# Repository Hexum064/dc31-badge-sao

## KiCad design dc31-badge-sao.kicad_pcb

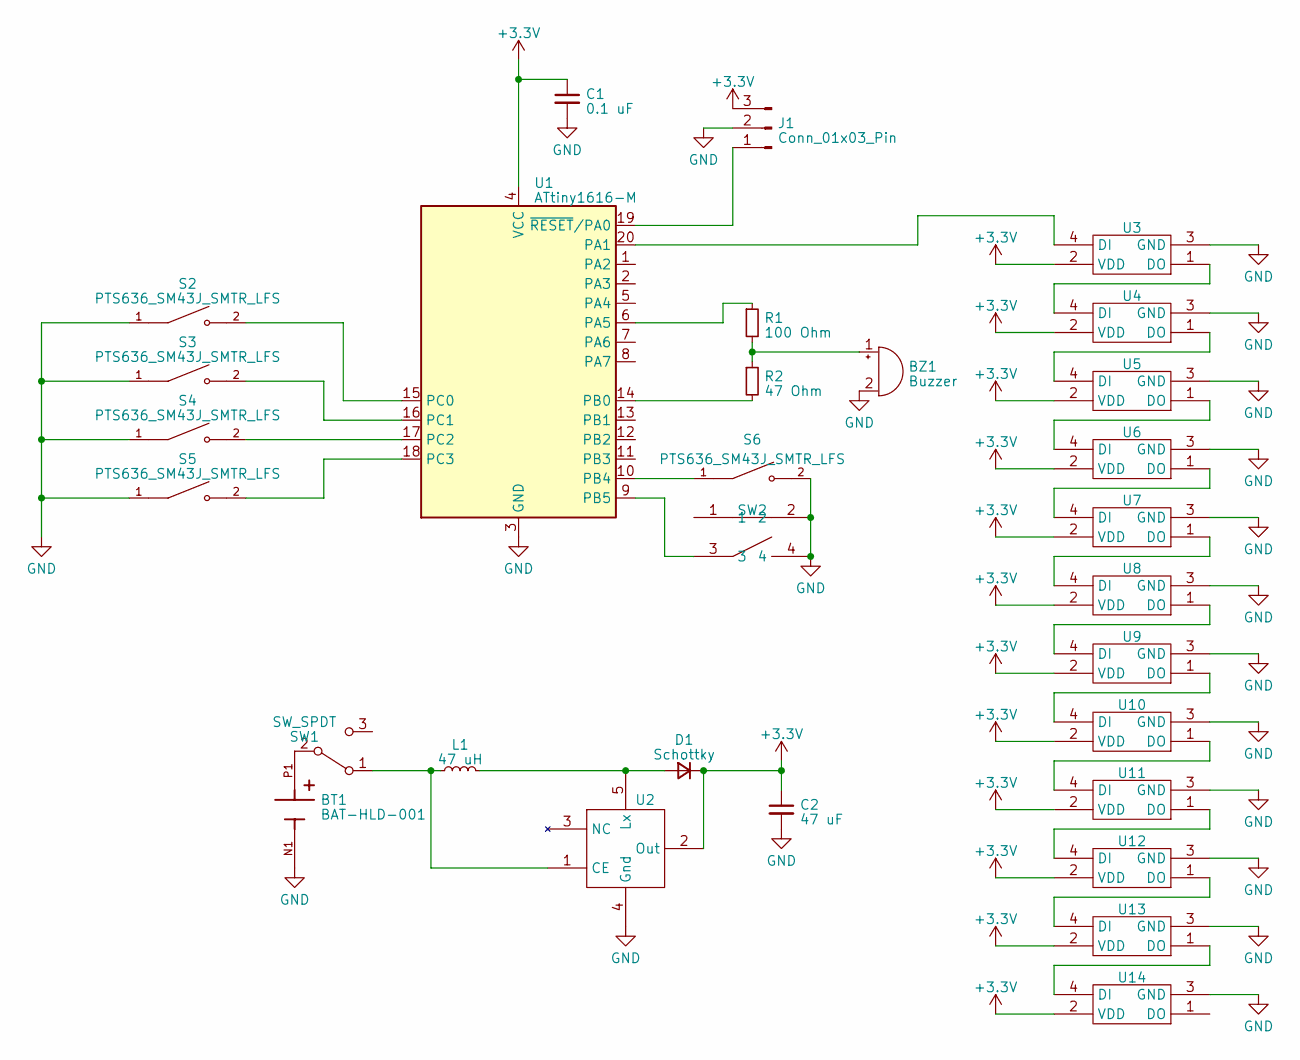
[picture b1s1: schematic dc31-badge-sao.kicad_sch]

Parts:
BT1: BAT-HLD-001; BAT_BAT-HLD-001; PARTREV C
BZ1: Buzzer; GSC1031YB-3V4000
C1: 0.1 uF; C_0603_1608Metric
C2: 47 uF; CP_EIA-3528-21_Kemet-B
D1: Schottky; D_SOD-323
J1: Conn_01x03_Pin; PinHeader_1x03_P2.54mm_Vertical
L1: 47 uH; L_0805_2012Metric
R1: 100 Ohm; R_0603_1608Metric
R2: 47 Ohm; R_0603_1608Metric
S2, S3, S4, S5, S6: PTS636_SM43J_SMTR_LFS; SW_PTS636_SM43J_SMTR_LFS; PARTREV 27 mar 19
SW1: SW_SPDT; MSS3VTR
SW2: TM-1627A
U1: ATtiny1616-M; VQFN-20-1EP_3x3mm_P0.4mm_EP1.7x1.7mm
U2: SOT-23-5
U3, U4, U5, U6, U7, U8, U9, U10, U11, U12, U13, U14: ws2812b-1010

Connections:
+3.3V: C1.1, C2.1, D1.1 (K), J1.3, L1.1, SW1.1 (A), U1.4 (VCC), U2.1 (CE), U2.2 (Out), U3.2 (VDD), U4.2 (VDD), U5.2 (VDD), U6.2 (VDD), U7.2 (VDD), U8.2 (VDD), U9.2 (VDD), U10.2 (VDD), U11.2 (VDD), U12.2 (VDD), U13.2 (VDD), U14.2 (VDD)
GND: BT1.N1, BZ1.2 (+), C1.2, C2.2, J1.2, S2.1, S3.1, S4.1, S5.1, S6.2, SW2.2, SW2.4, U1.3 (GND), U1.21 (GND), U2.4 (Gnd), U3.3 (GND), U4.3 (GND), U5.3 (GND), U6.3 (GND), U7.3 (GND), U8.3 (GND), U9.3 (GND), U10.3 (GND), U11.3 (GND), U12.3 (GND), U13.3 (GND), U14.3 (GND)
unnamed: BZ1.1 (-), R1.2, R2.1
unnamed: D1.2 (A), L1.2, U2.5 (Lx)
unnamed: J1.1, U1.19 (~RESET/PA0)
unnamed: BT1.P1, SW1.2 (B)
unnamed: U1.20 (PA1), U3.4 (DI)
unnamed: R1.1, U1.6 (PA5)
unnamed: R2.2, U1.14 (PB0)
unnamed: S6.1, U1.10 (PB4)
unnamed: SW2.3, U1.9 (PB5)
unnamed: S2.2, U1.15 (PC0)
unnamed: S3.2, U1.16 (PC1)
unnamed: S4.2, U1.17 (PC2)
unnamed: S5.2, U1.18 (PC3)
unnamed: U3.1 (DO), U4.4 (DI)
unnamed: U4.1 (DO), U5.4 (DI)
unnamed: U5.1 (DO), U6.4 (DI)
unnamed: U6.1 (DO), U7.4 (DI)
unnamed: U7.1 (DO), U8.4 (DI)
unnamed: U8.1 (DO), U9.4 (DI)
unnamed: U9.1 (DO), U10.4 (DI)
unnamed: U10.1 (DO), U11.4 (DI)
unnamed: U11.1 (DO), U12.4 (DI)
unnamed: U12.1 (DO), U13.4 (DI)
unnamed: U13.1 (DO), U14.4 (DI)

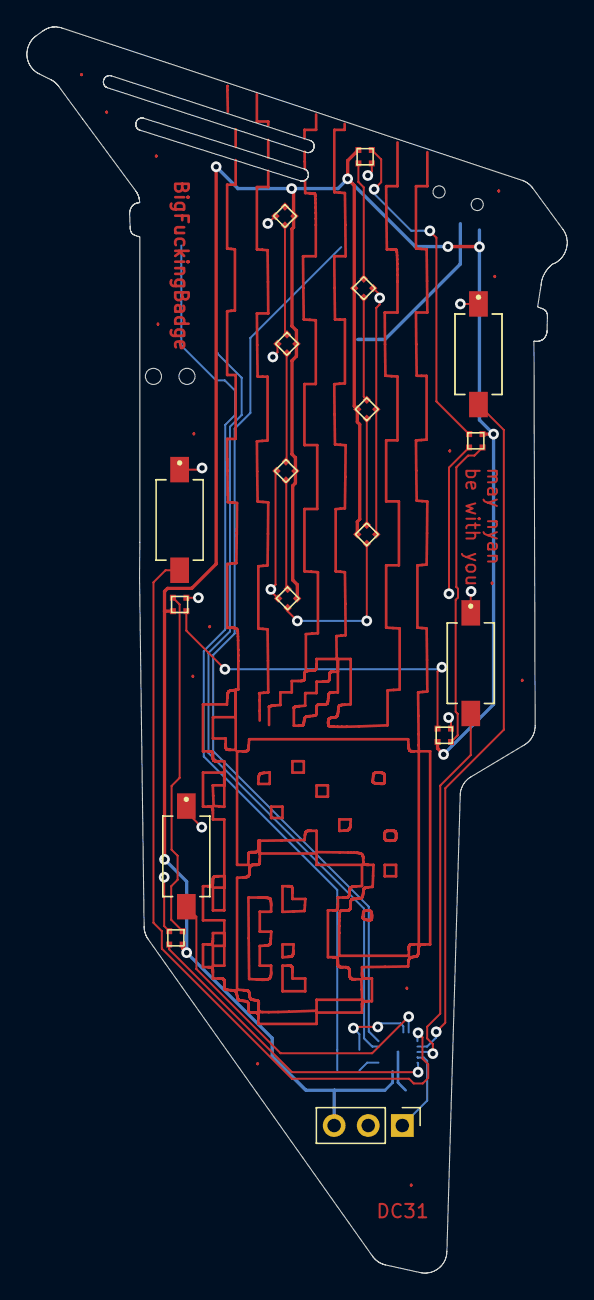
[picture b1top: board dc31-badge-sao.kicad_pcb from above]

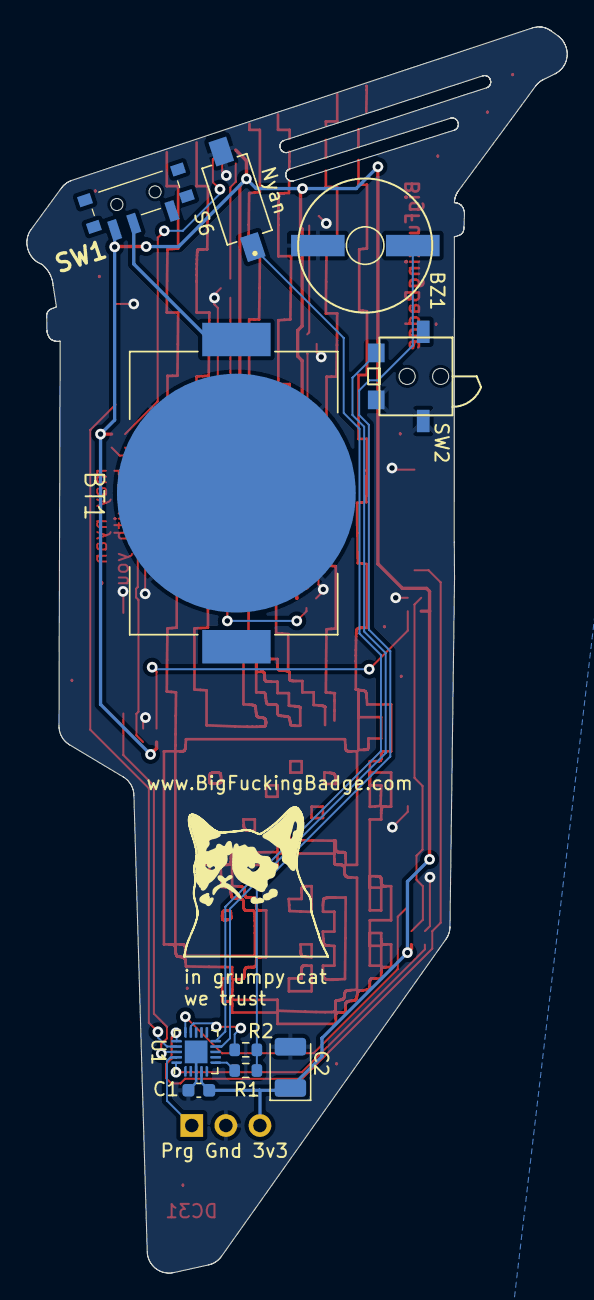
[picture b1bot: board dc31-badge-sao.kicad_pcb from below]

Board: 2 copper layers, 40.3 x 92.9 mm, 27 parts (10 on the bottom side), 25 nets.

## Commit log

2023-07-13 added a reset feature
2023-07-20 updates after receiving protos
